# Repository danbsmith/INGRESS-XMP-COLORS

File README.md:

This repository contains design files for a toy modeled after the shape of an XMP from the game Ingress.  In addition to the shape, it contains circuitry which will adjust the color of RGB LEDs using a potentiometer to match the colors associated with the levels of Ingress players.

The plastic base is designed in FreeCAD.

The circuit board is designed in KiCAD.

Please stay within the bounds of the license (found in LICENSE.txt) when using these files.

Feel free to contact me at the address in CONTRIB.txt, but include a relevant subject line so I know it is about this repository.

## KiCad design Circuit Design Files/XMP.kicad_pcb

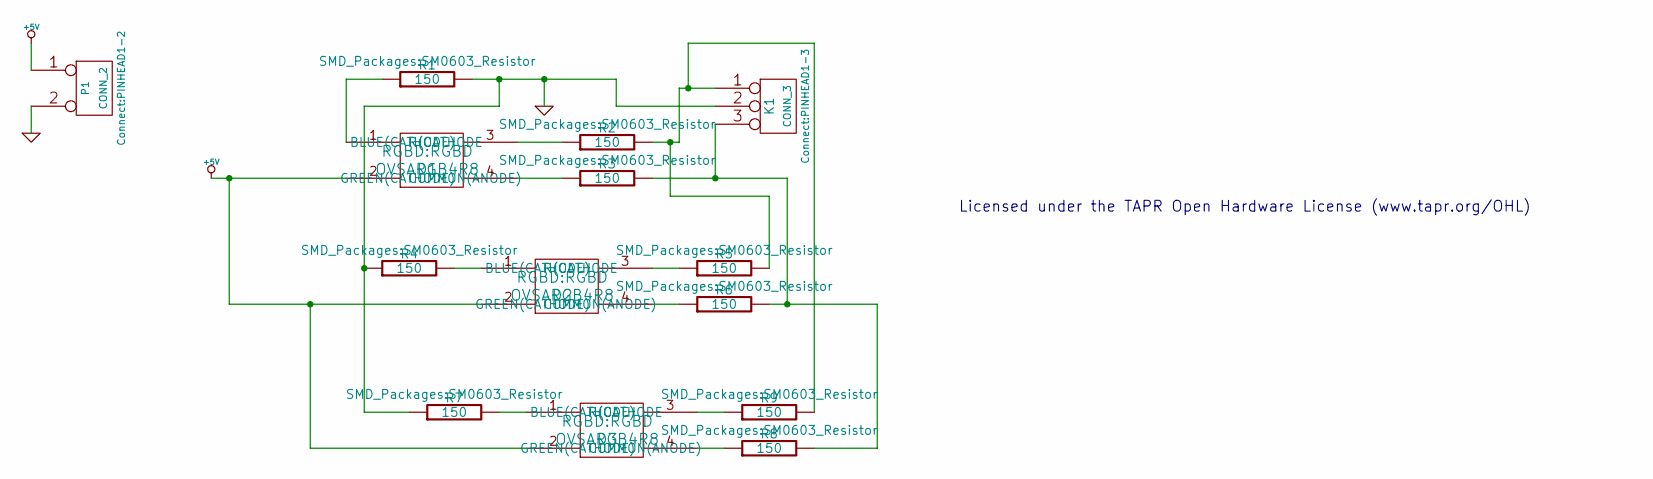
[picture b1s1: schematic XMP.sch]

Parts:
D1, D2, D3: OVSARGB4R8; RGBD
K1: CONN_3; PINHEAD1-3
P1: CONN_2; PINHEAD1-2
R1, R2, R3, R4, R5, R6, R7, R8, R9: 150; SM0603_Resistor

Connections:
+5V: D1.2 (COMMON(ANODE)), D2.2 (COMMON(ANODE)), D3.2 (COMMON(ANODE)), P1.1
GND: K1.2 (PM), P1.2 (PM), R1.2, R4.1, R7.1
unnamed: D1.1 (R(CATHODE), R1.1
unnamed: D1.3 (BLUE(CATHODE)), R2.1
unnamed: D1.4 (GREEN(CATHODE)), R3.1
unnamed: D2.1 (R(CATHODE), R4.2
unnamed: D2.3 (BLUE(CATHODE)), R5.1
unnamed: D2.4 (GREEN(CATHODE)), R6.1
unnamed: D3.1 (R(CATHODE), R7.2
unnamed: D3.3 (BLUE(CATHODE)), R9.1
unnamed: D3.4 (GREEN(CATHODE)), R8.1
unnamed: K1.1, R2.2, R5.2, R9.2
unnamed: K1.3, R3.2, R6.2, R8.2

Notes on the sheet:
Licensed under the TAPR Open Hardware License (www.tapr.org/OHL)

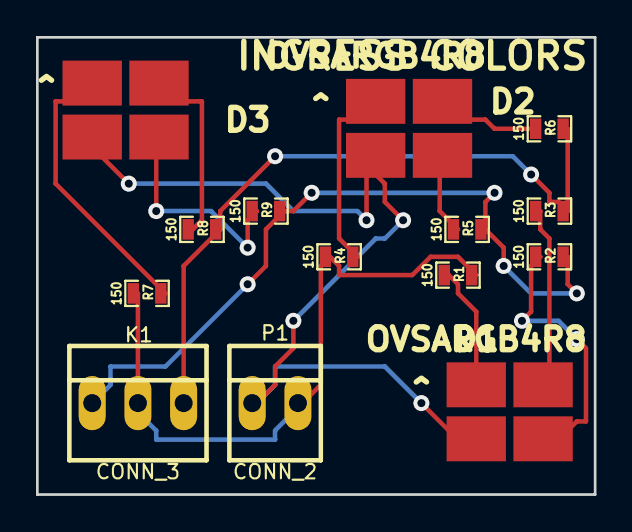
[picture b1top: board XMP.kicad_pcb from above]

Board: 2 copper layers, 31.0 x 25.4 mm, 14 parts (0 on the bottom side), 13 nets.

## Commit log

2013-04-19 Initial commit of the background information files and the Circuit Design Files.
2013-04-19 Updated circuit designs with the part number of the RGB LED in use.
2013-04-19 Added initial release of Base piece.
2013-04-19 Adjusted size of base to fit on Makerbot Replicator build platform.
2013-04-20 Added initial commit of XMP core piece to 3D design files.
2013-04-21 Made arbitrary changes to PCB to make it process properly on the fabrication service website.
2013-04-21 Altered readme for clarity.
2013-04-21 Added License information to documents.
2013-04-21 Changed XMP core 3D model to make the posts mate with the holes on the base.
2013-04-21 Added License information to metadata
2013-05-12 Improved version of 3D Design files in order to make sure that they fit together.
2013-05-18 I added a 3D piece to go on top of the stack to complete the XMP shell.
2014-02-09 Improved constraint consistency, enlarged fastener holes, temporarily removed mounting spots for potentiometer, cables.
2014-02-09 Updated circuit design files to fix issues with labeling (among other things)
2014-04-17 Updated 3D design files and added STLs for use in GitHub
